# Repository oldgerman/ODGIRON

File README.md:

# ODGIRON

## 关于

> 这是一个很久以前的项目，也是我刚学习stm32做的第一个项目，仅给老友们发车了10个套件，现将其所有软硬件资料开源
>
> Github仓库链接：https://github.com/oldgerman/ODGIRON

开源USB-C PD T12电烙铁，基于HAL库开发，STM32CubeIDE + STM32CubeMX

固件从 [ironOS](https://github.com/Ralim/IronOS) 修改而来，运行FreeRTOS，更换了主控，重新设计了主界面和多级菜单，更大的oled显示屏，分辨率128x32

双面板设计，电阻电容最小0603封装，焊接难度比0402小

前期准备几乎兼容所有QFN48、RAM ≥ 20KB、FLASH ≥ 128KB 的STM32芯片，但后期发现 F103 固件写不下了遂停止维护，主力适配 F401，当然如果你有能力，可自行移植到其他型号上

## 技术大纲

## 成品

## 硬件

### 配置

- 主控：STM32F103CBU6、STM32F401CCU6
- 屏幕：0.87inch OLED，SSD1316 分辨率128x32
- PD协议芯片：FUSB302B
- 加速度计：LIS3DH
- 功率计：INA226
- 电源管理：MP2456 + LDO 3.3V
- 温度测量：SGM8551 + MCP9700AT
- 功率MOS：AON7403（-30V/-29A）*2
- 外壳：尼龙3D打印

### PCB

### 原理图

### 外壳

## 软件

[固件版本更新日志](https://github.com/oldgerman/ODGIRON/blob/master/Notes/firmware_logs.md)

[固件升级方法](https://github.com/oldgerman/ODGIRON/blob/master/Notes/firmware_upgrade.md)

### 功能

- :heavy_check_mark:功率计

- :heavy_check_mark:自动休眠、运动唤醒

- :heavy_check_mark:温度功率曲线绘制

- :heavy_check_mark:USB固件升级

- :heavy_check_mark:多级菜单（可配置的参数太多，只列举几个）

  - 温度校准
  - 冷却休眠
  - 枚举PD挡位
  - ...

- :heavy_check_mark:断电保存设置

- 待开发

  - 多语言支持（目前仅支持中文）

  - ...

### BUG

ADC注入通道测量尖端的温度：STM32F401CCU6偶尔会向上抖动10度，同样的代码在STM32F103CBU6跑却很稳定，可能是ADC时钟频率、采样周期、转换周期不同导致，目前整不好了，但影响不大:)

## 致谢

> 感谢[@Miniware](http://www.miniware.com.cn/)开源的[TS100资料](http://www.minidso.com/forum.php?mod=viewthread&tid=892)
>
> 感谢[@Ralim](https://github.com/Ralim)开发的[ironOS](https://github.com/Ralim/IronOS)
>
> 感谢[@olikraus](https://github.com/olikraus)开发的[u8g2](https://github.com/olikraus/u8g2)
>
> 感谢[@Zanduino](https://github.com/Zanduino)开发的[INA](https://github.com/Zanduino/INA)

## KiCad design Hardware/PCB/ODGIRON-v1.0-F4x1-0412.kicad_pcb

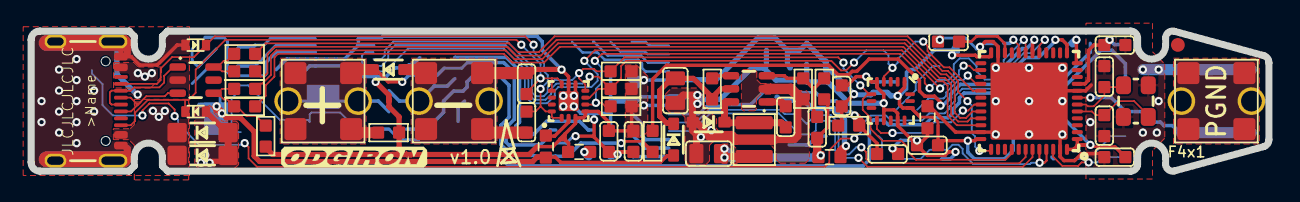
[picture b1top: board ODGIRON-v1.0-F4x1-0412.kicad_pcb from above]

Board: 2 copper layers, 89.8 x 10.2 mm, 124 parts (0 on the bottom side), 67 nets.

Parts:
AMP1: SGM8551XN5G/TR; SOT23-5
BUZ1: BUZZER_5020
C1, C2, C3, C4, C5, C6, C10, C11, C12, C13, C14, C16, C29: 0.1uF/50V; C0603
C7, C23: 4.7uF/16V; C0603
C8, C9: 10pF/50V; C0603
C15, C21, C22, C24, C31, C39: 1uF/16V; C0603
C17, C27: 10nF/50V; C0603
C18, C19: 470pF/50V; C0603
C20, C25, C26, C37: 10uF/10V; C0603
C30: 10uF/25V; C0805
C32: 2.2uF/16V; C0603
C33: 4.7uF/50V; C0805
C34, C35: 100pF/50V; C0603
CP1: FUSE_CLIPS_01
D1, D7, D9: B5819WS; SOD-323
D2, D5: SMF24A; SOD-123
D3: MMSZ5242BS-7-F; SOD-323
D6, D8: ESD5B5.0ST1; SOD-523
DA1: INA226; MSOP10
FB1, FB2, FB3, FB4, FB5: 1K; F0603
FID1, FID1#2: FIDUCIAL; FIDUCIAL_1MM
J3: USB-C-16P
JP1: SMT-JUMPER_2_NO_SILK
L1: 33uH CBC3225T330KR; SMD,3.2X2.5X2.5MM
LCD1: 0.87inch SSD1306; 0.87INCH_128X32_OLED_SSD1306
LOGO1: OSHW-LOGONO_SILK; DUMMY
PAD1, PAD2, PAD3, PAD4, PAD5, PAD6, PAD7, PAD8, PAD9, PAD10, PAD11, PAD12: PADTP16SQ; TP16SQ
Q2, Q3: AON7403; DFN8P-0.65-3X3X0.8MM
Q4: S8050; SOT23-3
R1, R13: 32.4K; R0603
R2: 124K; R0603
R3, R10, R16, R18, R19, R22, R25, R35: 4.7K; R0603
R4: 1.5K; R0603
R5, R6, R27, R28: 22R; R0603
R7, R12, R23, R41, R45: 1K; R0603
R8, R20, R42: 100K; R0603
R9, R11, R14, R38: 10K; R0603
R17: 560K; R0603
R24: 10mR ±1% ±50ppm/℃; R1206
R36, R37: 10R; R0603
R43: 2.37K ±0.1% ±25ppm/℃; R0603
R44: 750K ±0.1% ±25ppm/℃; R0603
S1, S2, S3, S5: TACTILE_SWITCH_SMD
T1: HAKKO_T12_K-TYPE_WITH_FUSE_CLIPS_X2
TP1: PGND; TESTPOINT_ROUND_2MM
U1: FUSB302BMPX; QFN14-2.5X2.5MM
U3: STM32F4x1CxU6; QFN48_7X7MM_0.5MM
U4: MP2456GJ; SOT23-6
U5: MCP9700AT-E/TT,or LM50CIM3X; SOT23-3@1
U6: MCP1700T-3302E/TT; SOT23-3
U8: LIS3DH; LGA-16-3X3
U$3: CREATIVE_COMMONS
VD1: USBLC6-2SC6; SOT23-6
ZO1: 8MHz; 3.2X2.5_KX-7

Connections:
3.9V: C30.1, C35.1, FB1.1, L1.2, R2.1
+3V3: C2.1, C4.1, C5.1, C12.2, C13.2, C14.2, C15.1, C20.2, C23.2, C24.2, C37.2, C39.2, DA1.6, FB2.2, FB3.2, LCD1.5, LCD1.8, R3.1, R4.2, R13.2, R16.1, R18.2, R19.2, R22.2, R23.2, R25.1, R38.1, S3.3, S3.4, U1.3, U1.4, U3.1, U3.24, U3.36, U3.48, U5.1, U6.2, U8.1, U8.14
AMP+: AMP1.3, R42.1
AMP-: AMP1.4, C34.2, R43.1, R44.2
BS: C29.1, U4.1
CC1: C18.1, D8.K, J3.A5, U1.1, U1.14
CC2: C19.1, D6.K, J3.B5, U1.10, U1.11
D+: J3.A6, J3.B6, VD1.3
D-: J3.A7, J3.B7, VD1.1
DCDC_IN: C33.1, D1.C, R20.2, U4.5
EN: R20.1, U4.4
GND: AMP1.2, BUZ1.-, C2.2, C3.2, C4.2, C5.2, C6.2, C7.2, C8.1, C9.1, C10.2, C11.1, C12.1, C13.1, C14.1, C15.2, C16.1, C18.2, C19.2, C20.1, C23.1, C24.1, C25.2, C26.2, C27.2, C30.2, C31.1, C32.2, C33.2, C37.1, C39.1, D2.A, D5.A, D6.A, D7.A, D8.A, D9.A, DA1.1, DA1.2, DA1.7, FB4.1, FB4.2, J3.GND, J3.GND2, J3.SHLD1, J3.SHLD2, J3.SHLD5, J3.SHLD8, JP1.1, LCD1.7, PAD5.TP, PAD6.TP, PAD7.TP, PAD8.TP, Q4.2, R1.1, R8.2, R12.1, R17.1, R43.2, S1.1, S1.2, S2.1, S2.2, S5.1, S5.2, T1.1A1, T1.1B1, U1.8, U1.9, U1.THERMAL, U3.8, U3.23, U3.35, U3.47, U3.P$1, U4.2, U5.3, U6.1, U8.5, U8.10, U8.12, VD1.2, ZO1.2, ZO1.4
LDO_IN: C31.2, FB1.2, U6.3
unnamed: R4.1, R5.1, R27.1, VD1.4
unnamed: R7.2, S3.1, S3.2
unnamed: D3.C, Q2.1, Q2.2, Q2.3, Q3.1, Q3.2, Q3.3
unnamed: C21.1, LCD1.1
unnamed: D3.A, Q2.4, Q3.4, R10.2, R35.1
unnamed: C22.1, LCD1.3
unnamed: C11.2, FB2.1, U3.9
unnamed: C3.1, R9.2, S1.3, S1.4
unnamed: C21.2, LCD1.2
unnamed: C6.1, R14.2, S2.3, S2.4
unnamed: C22.2, LCD1.4
unnamed: C25.1, LCD1.13
unnamed: LCD1.12, R17.2
unnamed: C26.1, LCD1.14
unnamed: Q4.1, R11.1
unnamed: C35.2, R1.2, R2.2, U4.3
unnamed: C16.2, Q4.3, R35.2
unnamed: C17.1, R11.2, R12.2
unnamed: AMP1.5, FB3.1
unnamed: R6.1, R28.1, VD1.6
unnamed: FB5.1, U1.2
unnamed: JP1.2, U3.20
unnamed: C1.1, DA1.10, R36.1
unnamed: C1.2, DA1.9, R37.1
unnamed: R41.2, U5.2
NRST: C10.1, R23.1, S5.3, S5.4, U3.7
OSC_IN: C8.2, U3.5, ZO1.3
OSC_OUT: C9.2, U3.6, ZO1.1
OUT: AMP1.1, C34.1, R44.1, R45.2
PA2/ADC2: R41.1, U3.12
PA3/T2C4: C17.2, U3.13
PA7/T1CH1N/T3C2: BUZ1.+, U3.17
PA8/SCL3: DA1.5, R3.2, U1.6, U3.29, U8.4
PA10/IT_ACCEL_2: U3.31, U8.9
PA11/USB_DM: R6.2, U3.32
PA12/USB_DP: R5.2, U3.33
PA13/SWDIO: R27.2, U3.34
PA14/SWCLK: R28.2, U3.37
PB0/ADC8: R45.1, U3.18
PB1/IT_FUSB302: R16.2, U1.5, U3.19
PB4/SDA3: DA1.4, R25.2, U1.7, U3.40, U8.6
PB6/SCL1: LCD1.10, R19.1, U3.42
PB7/SDA1: LCD1.11, R18.1, U3.43
PB8&BOOT0_S3: R7.1, R8.1, U3.44, U3.45
PB9/S1: R9.1, U3.46
PB13/IT_INA226: DA1.3, R38.2, U3.26
PB15/S2: R14.1, U3.28
PGND: CP1.1A, CP1.1B, PAD9.TP, PAD10.TP, PAD11.TP, PAD12.TP, TP1.P$1
RES_3.3V: C7.1, LCD1.9, R22.1
SW: C29.2, D7.C, L1.1, U4.6
T12+: C27.1, D9.C, PAD1.TP, PAD2.TP, PAD3.TP, PAD4.TP, Q3.5, Q3.6, Q3.7, Q3.8, Q3.9, R13.1, R42.2, T1.1A, T1.1B
VBUS-C: D1.A, FB5.2, Q2.5, Q2.6, Q2.7, Q2.8, Q2.9, R10.1, R24.1, R37.2
VCAP1: C32.1, U3.22
VUSB_IN: D2.C, D5.C, DA1.8, J3.VBUS1, J3.VBUS2, R24.2, R36.2

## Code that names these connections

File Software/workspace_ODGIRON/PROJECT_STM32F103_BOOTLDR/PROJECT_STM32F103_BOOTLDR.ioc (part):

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Mcu.Name=STM32F103CBUx
Mcu.Package=UFQFPN48
Mcu.UserName=STM32F103CBUx
PA11.Mode=Device
PA11.Signal=USB_DM
PA12.Mode=Device
PA12.Signal=USB_DP
PA13.Mode=Serial_Wire
PA13.Signal=SYS_JTMS-SWDIO
PA14.Mode=Serial_Wire
PA14.Signal=SYS_JTCK-SWCLK
PB1.GPIOParameters=GPIO_PuPd,GPIO_Label,GPIO_ModeDefaultEXTI
PB1.GPIO_Label=IT_FUSB302B
PB1.GPIO_ModeDefaultEXTI=GPIO_MODE_IT_FALLING
PB1.GPIO_PuPd=GPIO_PULLUP
PB1.Signal=GPXTI1
PB15.GPIOParameters=GPIO_PuPd,GPIO_Label
PB15.GPIO_Label=KEY_OK
PB15.GPIO_PuPd=GPIO_PULLUP
PB15.Signal=GPIO_Input
PB6.GPIOParameters=GPIO_Label
PB6.GPIO_Label=SCL1
PB6.Mode=I2C
PB6.Signal=I2C1_SCL
PB7.GPIOParameters=GPIO_Label
PB7.GPIO_Label=SDA1
PB7.Mode=I2C
PB7.Signal=I2C1_SDA
PB8.GPIOParameters=GPIO_PuPd,GPIO_Label
PB8.GPIO_Label=KEY_B
PB8.GPIO_PuPd=GPIO_NOPULL
PB8.Signal=GPIO_Input
PB9.GPIOParameters=GPIO_PuPd,GPIO_Label
PB9.GPIO_Label=KEY_A
PB9.GPIO_PuPd=GPIO_PULLUP
PB9.Signal=GPIO_Input
PD0-OSC_IN.Mode=HSE-External-Oscillator
PD0-OSC_IN.Signal=RCC_OSC_IN
PD1-OSC_OUT.Mode=HSE-External-Oscillator
PD1-OSC_OUT.Signal=RCC_OSC_OUT
RCC.SYSCLKFreq_VALUE=72000000
RCC.SYSCLKSource=RCC_SYSCLKSOURCE_PLLCLK
board=custom

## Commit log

2021-08-09 2 commit
2021-08-09 3 commit
2021-08-09 4 commit
2021-08-10 5 commit, 添加菜单滚动栏动画
2021-08-10 6 commit，修复重启进入DFU功能的USB无法识别
2021-08-11 7 commit，增加菜单栏迭代跟随运动，主页调温的衔接动效
2022-04-04 移除F103CBU6的固件
2022-04-04 更新固件
2022-04-24 添加校准目标温度可调功能
2022-04-27 添加温度失控保护
2022-12-01 添加ODGIRON_20210624之前的相关文件
2023-07-02 2023-07-02_11:59
2023-07-02 2023-07-02_11:01

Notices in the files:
parts and their libraries:
https://creativecommons.org/licenses/by-sa/4.0
Released under the Creative Commons Attribution Share-Alike 4.0 License
